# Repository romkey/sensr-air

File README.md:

# sensr-air

Hardware design and test firmware for a small air quality sensor PCB with:

| Sensor | Function | I2C address |
|--------|----------|-------------|
| Sensirion SGP41 | VOC index / NOx index | 0x59 |
| Sensirion STCC4 | CO2 | 0x64 (0x65 if ADDR is high) |
| Sensirion SFA40 | formaldehyde (HCHO) | 0x5D |
| Sensirion SHT40 | temperature / humidity | none — connected to the STCC4's private I2C bus and read through the STCC4 |
| Bosch BMV080 | PM1 / PM2.5 / PM10 | 0x54 |

Boards up to `hw/air-stcc4/0.3.0` carry an SGP40 (VOC only) instead of the
SGP41 and have no SFA40. The two SGP parts share address 0x59; the test
firmwares read the SGP4x feature set at startup to tell them apart, so one
build runs on either revision.

This is a 3.3 V board with no voltage regulator — don't use it with 5 V
circuits. To simplify it, the board is opinionated about I2C
addresses and doesn't expose address selection pins for chips that
have them. For reliability I don't recommend putting too many chips on
one I2C bus.

## AI Disclosure

The board was designed by a human. CI and firmware were generated by AI.

## Hardware

Board designs live under [hw/](hw/), one subdirectory per board with a
subdirectory per version:

- [hw/air-stcc4/](hw/air-stcc4/) — STCC4 + SHT40 breakout
- [hw/air/](hw/air/) — earlier SCD40 + BME680 board

### KiCAD CI

The [KiCAD workflow](.github/workflows/kicad.yml) runs
[ci/kicad-check.sh](ci/kicad-check.sh), which runs ERC on every schematic and
DRC on every PCB of the latest version of each board under `hw/`. Only errors
fail the check; warnings are ignored. Boards or versions containing a
`.ci-kicad-ignore` file are skipped.

Run it locally with KiCAD 8+ installed:

```sh
./ci/kicad-check.sh
```

### kilint CI

The [kilint workflow](.github/workflows/kilint.yml) runs
[kilint](https://github.com/romkey/kilint), a linter for KiCAD project
conventions that ERC and DRC don't cover (title blocks, reference designators,
mounting holes, part number fields, net classes, and so on). It runs only when
[BOFFF.md](BOFFF.md) is present, and lints the single board that BOFFF.md's
`repository_path` points at via [ci/kilint-check.sh](ci/kilint-check.sh).
Older boards under `hw/` predate these conventions and are not checked.

Rule configuration lives in [.kilint.yml](.kilint.yml). kilint has no tagged
releases yet, so the workflow installs it from `main`; pin `KILINT_REF` in the
workflow once it does.

Run it locally:

```sh
pip install git+https://github.com/romkey/kilint
./ci/kilint-check.sh
```

### BOFFF

[BOFFF.md](BOFFF.md) is this board's machine-readable fabrication/form-factor
description (Bill of Form, Fit and Features) - it's a tldr; for
important facts about the board. The [BOFFF workflow](.github/workflows/bofff.yml) does nothing but
assert the file exists, so the BOFFF badge above is green whenever the repo
carries one.

## Test firmware

Each firmware directory contains a test program that exercises all of the
board's sensors, a README, and (where possible) a docker compose file to
build it. All of them print/report readings from each sensor so you can
verify a freshly assembled board.

| Directory | Platform | SGP41 | STCC4 | SFA40 | SHT40 (via STCC4) | BMV080 |
|-----------|----------|-------|-------|-------|-------------------|--------|
| [firmware/circuitpython/](firmware/circuitpython/) | CircuitPython 9+ | yes | yes | yes³ | yes | presence check only¹ |
| [firmware/arduino/](firmware/arduino/) | Arduino / ESP32 | yes | yes | yes | yes | yes |
| [firmware/esphome/](firmware/esphome/) | ESPHome / ESP32 | yes | yes² | yes⁴ | yes² | yes |

¹ Bosch only ships the BMV080 driver as closed-source precompiled static
libraries for specific MCU toolchains, so no CircuitPython driver exists.

² ESPHome has no upstream STCC4 support; this repo includes a local
[external component](firmware/esphome/components/stcc4/) for it.

³ Via [romkey/circuitpython-sfa40](https://github.com/romkey/circuitpython-sfa40).

⁴ ESPHome's `sfa40` component landed upstream after 2026.8, so the ESPHome
build uses the beta channel until a stable release includes it.

CI builds all three firmwares on every push
([CircuitPython](.github/workflows/circuitpython.yml),
[Arduino](.github/workflows/arduino.yml),
[ESPHome](.github/workflows/esphome.yml)).

## License

Hardware designs are licensed under the
[CERN Open Hardware Licence v2 Permissive](https://ohwr.org/cern_ohl_p_v2.txt).
Firmware is licensed under the [MIT License](https://opensource.org/license/mit).

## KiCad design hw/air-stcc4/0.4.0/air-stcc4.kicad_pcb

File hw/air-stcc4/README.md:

# Sensr Air STCC4

This breakout board has Sensirion's new CO2 sensor, the STCC4, as well as an SHT40 temperature/humidity sensor. The board also has two STEMMAQT/Qwiic connectors and a five pin header with power, I2C and the STCC4's address select pin.

This is a 3.3V board and has no voltage regulator, so don't use it with 5V circuits!

It also has a power LED.

The STCC4 has a selectable I2C address depending on the state of the ADDR line.  The ADDR line has a weak pulldown resistor so that the STCC4's default I2C address is 0x64. If ADDR is high, the address will be 0x65.

The SHT40 is not directly accessible from the I2C bus. Instead it connects to a private second I2C bus with the STCC4. Its values may be read through the STCC4.

## 0.1.0 Hardware

## Firmware

Example program in CircuitPython:

```
import time
import board
import busio
from adafruit_stcc4 import STCC4

# Initialize I2C bus
i2c = busio.I2C(board.SCL, board.SDA)

# Initialize STCC4 sensor
sensor = STCC4(i2c)

print("STCC4 CO2 Sensor Test")
print("=" * 50)

# Print sensor information
print(f"Serial Number: {sensor.serial_number}")
print(f"Firmware Version: {sensor.firmware_version[0]}.{sensor.firmware_version[1]}")
print(f"SHT40 Available: {sensor.sht40_available}")
print()

# Read CO2, temperature, and humidity measurements
print("Environmental Measurements:")
print("-" * 30)

while True:
    co2 = sensor.co2
    print(f"Reading {i+1:2d}: CO2: {co2:6.1f} ppm")
        
    if sensor.sht40_available:
       temperature, humidity = sensor.measure_temperature_humidity()
       print(f"           Temp: {temperature:5.1f}°C, Humidity: {humidity:5.1f}%")
    else:
       print("           SHT40 not available - no temp/humidity data")
        
    print()
        
    time.sleep(2)  # Wait 2 seconds between readings

print("Test complete!")
```

## License

Please see the top level [README](../../README.md) for license information.

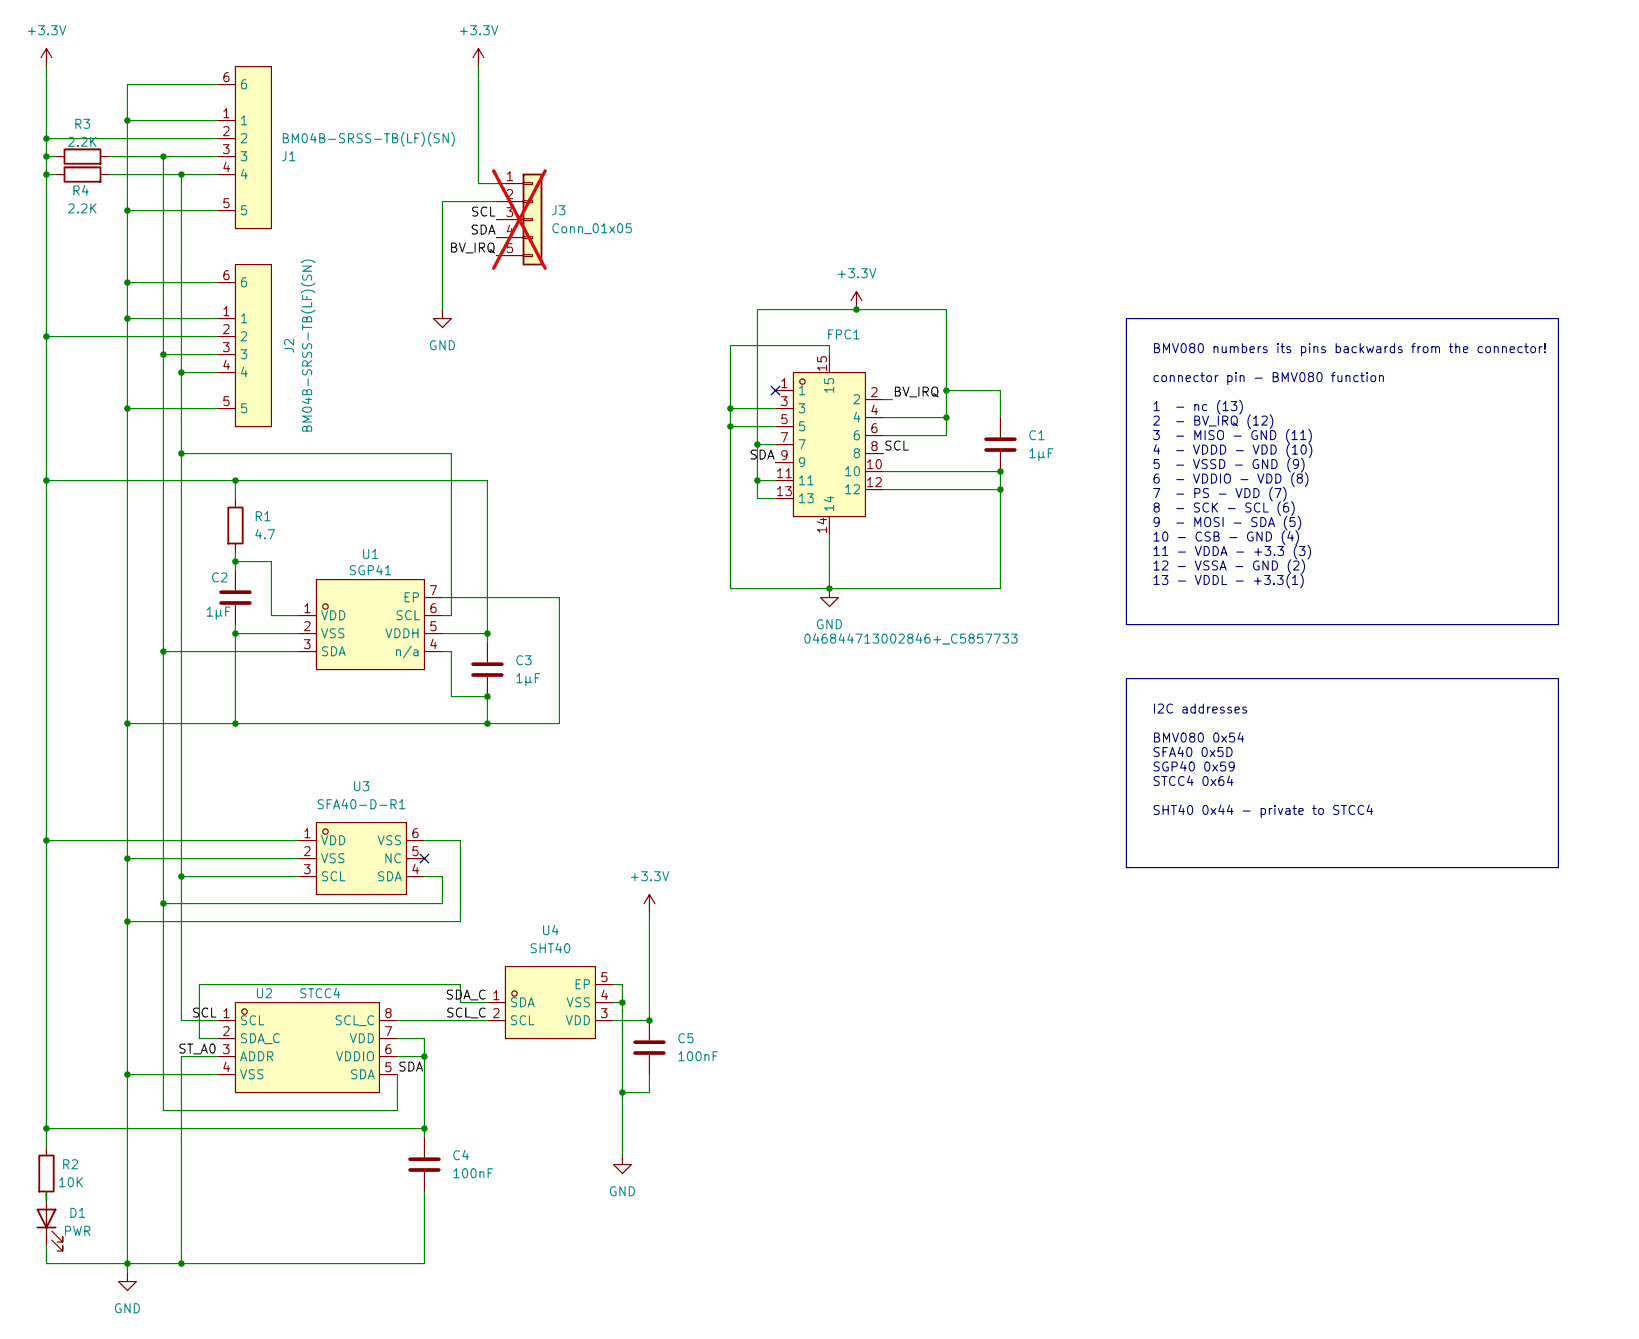
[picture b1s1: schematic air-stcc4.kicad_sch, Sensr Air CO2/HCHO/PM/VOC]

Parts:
C1, C2, C3: 1µF; C_0402_1005Metric_Pad0.74x0.62mm_HandSolder; LCSC Part C52923
C4, C5: 100nF; C_0402_1005Metric_Pad0.74x0.62mm_HandSolder; LCSC Part C1525
D1: PWR; LED_0603_1608Metric_Pad1.05x0.95mm_HandSolder; LCSC Part C2286
FPC1: 046844713002846+_C5857733; FPC-SMD_13P-P0.60_046844713002846-1; LCSC Part C5857733
J1, J2: BM04B-SRSS-TB(LF)(SN); CONN-SMD_4P-P1.00_SM04B-SRSS-TB-LF-SN; LCSC Part C160404
J3: Conn_01x05; PinSocket_1x05_P2.54mm_Vertical; not fitted
R1: 4.7; R_0603_1608Metric_Pad0.98x0.95mm_HandSolder; LCSC Part C23164
R2: 10K; R_0402_1005Metric_Pad0.72x0.64mm_HandSolder; LCSC Part C25744
R3, R4: 2.2K; R_0402_1005Metric_Pad0.72x0.64mm_HandSolder; LCSC Part C25879
U1: SGP41; DFN-6_L2.4-W2.4-P0.80-TL-EP; LCSC Part C3659325
U2: STCC4; LAG-8_L4.0-W3.0-P1.15-TL; LCSC Part C49191471
U3: SFA40-D-R1; SENSOR-SMD_SFA40-D-R1; LCSC Part C54863645
U4: SHT40; DFN-4_L1.5-W1.5-P0.80-TL-EP; LCSC Part C2848306

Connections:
+3.3V: C1.1, C3.1, C4.1, C5.1, FPC1.4, FPC1.6, FPC1.7, FPC1.11, FPC1.13, J1.2, J2.2, J3.1, R1.1, R2.1, R3.1, R4.1, U1.5 (VDDH), U2.6 (VDDIO), U2.7 (VDD), U3.1 (VDD), U4.3 (VDD)
/BV_IRQ: FPC1.2, J3.5
/SCL: FPC1.8, J1.4, J2.4, J3.3, R4.2, U1.6 (SCL), U2.1 (SCL), U3.3 (SCL)
/SCL_C: U2.8 (SCL_C), U4.2 (SCL)
/SDA: FPC1.9, J1.3, J2.3, J3.4, R3.2, U1.3 (SDA), U2.5 (SDA), U3.4 (SDA)
/SDA_C: U2.2 (SDA_C), U4.1 (SDA)
GND: C1.2, C2.2, C3.2, C4.2, C5.2, D1.1 (K), FPC1.3, FPC1.5, FPC1.10, FPC1.12, FPC1.14, FPC1.15, J1.1, J1.5, J1.6, J2.1, J2.5, J2.6, J3.2, U1.2 (VSS), U1.4 (n/a), U1.7 (EP), U2.3 (ADDR), U2.4 (VSS), U3.2 (VSS), U3.6 (VSS), U4.4 (VSS), U4.5 (EP)
unnamed: D1.2 (A), R2.2
unnamed: C2.1, R1.2, U1.1 (VDD)

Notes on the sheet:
BMV080 numbers its pins backwards from the connector! connector pin - BMV080 function 1 - nc (13) 2 - BV_IRQ (12) 3 - MISO - GND (11) 4 - VDDD - VDD (10) 5 - VSSD - GND (9) 6 - VDDIO - VDD (8) 7 - PS - VDD (7) 8 - SCK - SCL (6) 9 - MOSI - SDA (5) 10 - CSB - GND (4) 11 - VDDA - +3.3 (3) 12 - VSSA - 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
I2C addresses BMV080 0x54 SFA40 0x5D SGP40 0x59 STCC4 0x64 SHT40 0x44 - private to STCC4

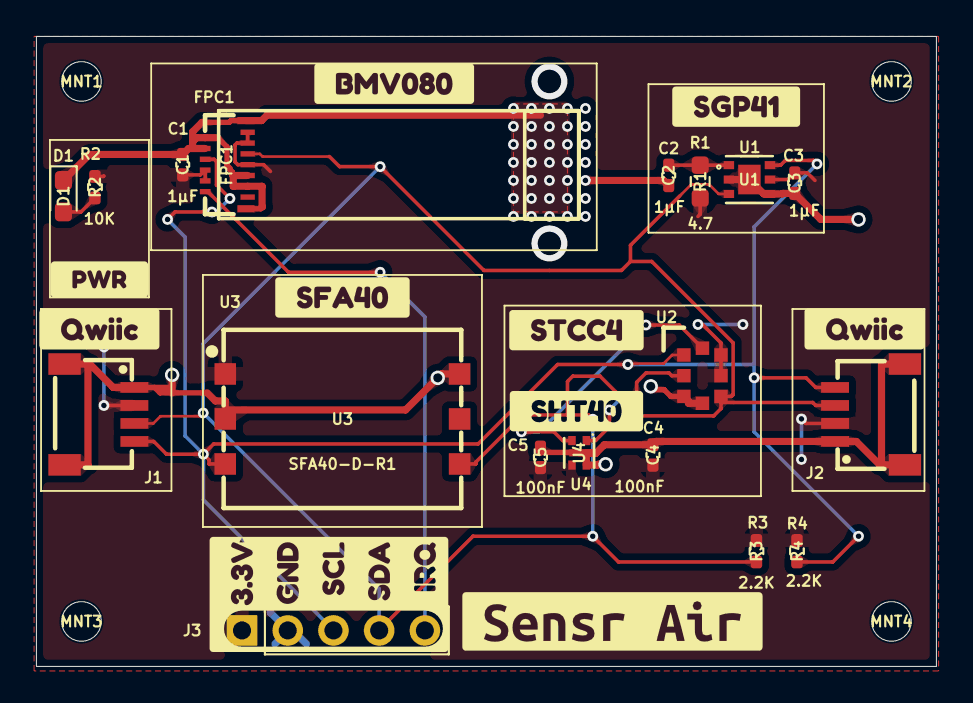
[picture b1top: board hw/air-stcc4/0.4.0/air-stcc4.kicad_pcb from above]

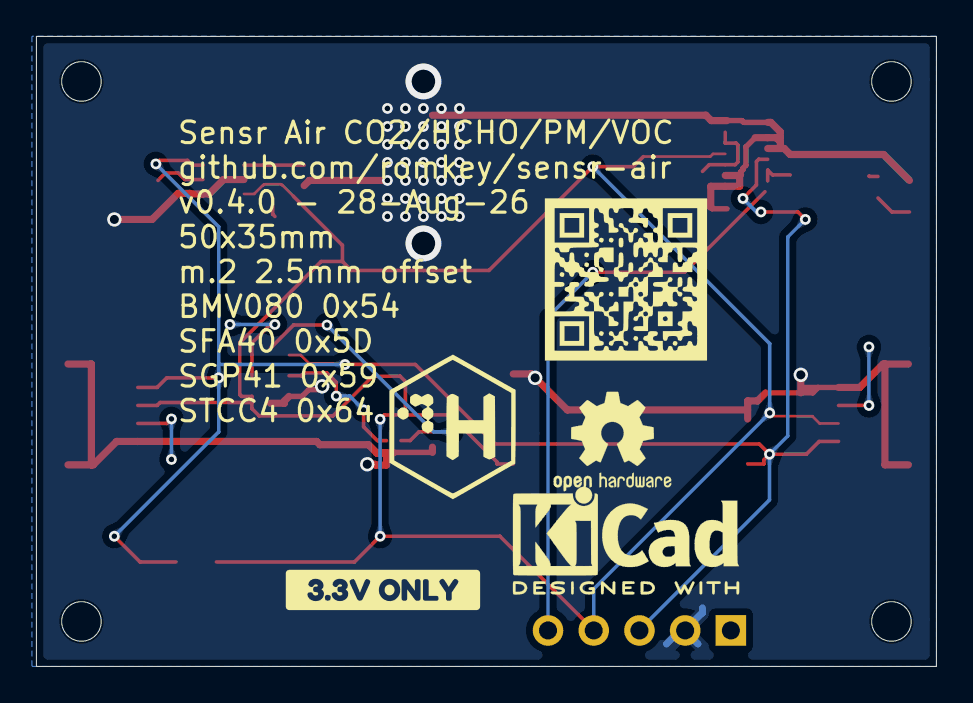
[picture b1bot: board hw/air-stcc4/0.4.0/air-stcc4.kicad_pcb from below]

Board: 2 copper layers, 50.0 x 35.0 mm, 37 parts (5 on the bottom side), 9 nets.

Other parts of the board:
GRPH1: LOGO
GRPH2: CTRLH Logo
GRPH3: OSHW-Logo2_7.3x6mm_SilkScreen
GRPH4: KiCad-Logo2_5mm_SilkScreen
MNT1, MNT2, MNT3, MNT4: MountingHole_2.2mm_M2
kobee-studio-1: GRPH4; kobee-studio-6A887D6C
kobee-studio-2: GRPH5; kobee-studio-6A887DEC
kobee-studio-3: G***; kobee-studio-6A91A728
kobee-studio-4: GRPH8; kobee-studio-6A887E41
kobee-studio-5: GRPH7; kobee-studio-6A887E5F
kobee-studio-6: GRPH9; kobee-studio-6A887E13
kobee-studio-6A91B03A: G***; kobee-studio-6A91B03A
kobee-studio-7: GRPH6; kobee-studio-6A8882DF
kobee-studio-8: GRPH10; kobee-studio-6A887E32
kobee-studio-9: G***; kobee-studio-6A91A7CE
kobee-studio-10: GRPH11; kobee-studio-6A887EAF

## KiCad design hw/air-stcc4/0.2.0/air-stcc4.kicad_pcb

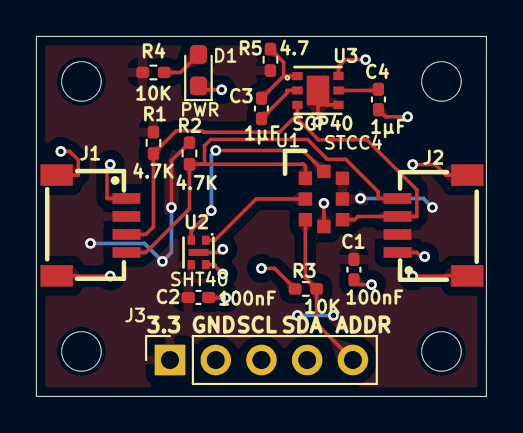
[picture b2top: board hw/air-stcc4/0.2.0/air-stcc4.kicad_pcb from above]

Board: 2 copper layers, 25.0 x 20.0 mm, 21 parts (1 on the bottom side), 11 nets.

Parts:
C1, C2: 100nF; C_0402_1005Metric_Pad0.74x0.62mm_HandSolder
C3, C4: 1µF; C_0402_1005Metric_Pad0.74x0.62mm_HandSolder
D1: PWR; LED_0603_1608Metric_Pad1.05x0.95mm_HandSolder
GRPH1: CTRLH Logo
J1, J2: BM04B-SRSS-TB(LF)(SN); CONN-SMD_4P-P1.00_SM04B-SRSS-TB-LF-SN
J3: Conn_01x05; PinSocket_1x05_P2.54mm_Vertical
M1, M2, M3, M4: MountingHole_2.2mm_M2
R1, R2: 4.7K; R_0402_1005Metric_Pad0.72x0.64mm_HandSolder
R3, R4: 10K; R_0402_1005Metric_Pad0.72x0.64mm_HandSolder
R5: 4.7; R_0402_1005Metric_Pad0.72x0.64mm_HandSolder
U1: STCC4; LAG-8_L4.0-W3.0-P1.15-TL
U2: SHT40; DFN-4_L1.5-W1.5-P0.80-TL-EP
U3: SGP40; DFN-6_L2.4-W2.4-P0.80-TL-EP

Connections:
+3.3V: C1.1, C2.1, J1.2, J2.2, J3.1, R1.1, R2.1, R4.1, R5.1, U1.6 (VDDIO), U1.7 (VDD), U2.3 (VDD)
/ADDR: J3.5, R3.1, U1.3 (ADDR)
/SCL_C: U1.8 (SCL_C), U2.2 (SCL)
/SDA_C: U1.2 (SDA_C), U2.1 (SDA)
GND: C1.2, C2.2, C4.2, D1.1 (K), J1.1, J1.5, J1.6, J2.1, J2.5, J2.6, J3.2, R3.2, U1.4 (VSS), U2.4 (VSS), U2.5 (EP), U3.4 (n/a), U3.6 (SCL), U3.7 (GND)
unnamed: D1.2 (A), R4.2
unnamed: J1.4, J2.4, R2.2, U1.1 (SCL)
unnamed: J1.3, J2.3, R1.2, U1.5 (SDA), U3.3 (SDA)
unnamed: C3.1, R5.2, U3.1 (VDD)
unnamed: C4.1, U3.5 (VDDH)
unnamed: C3.2, U3.2 (VSS)

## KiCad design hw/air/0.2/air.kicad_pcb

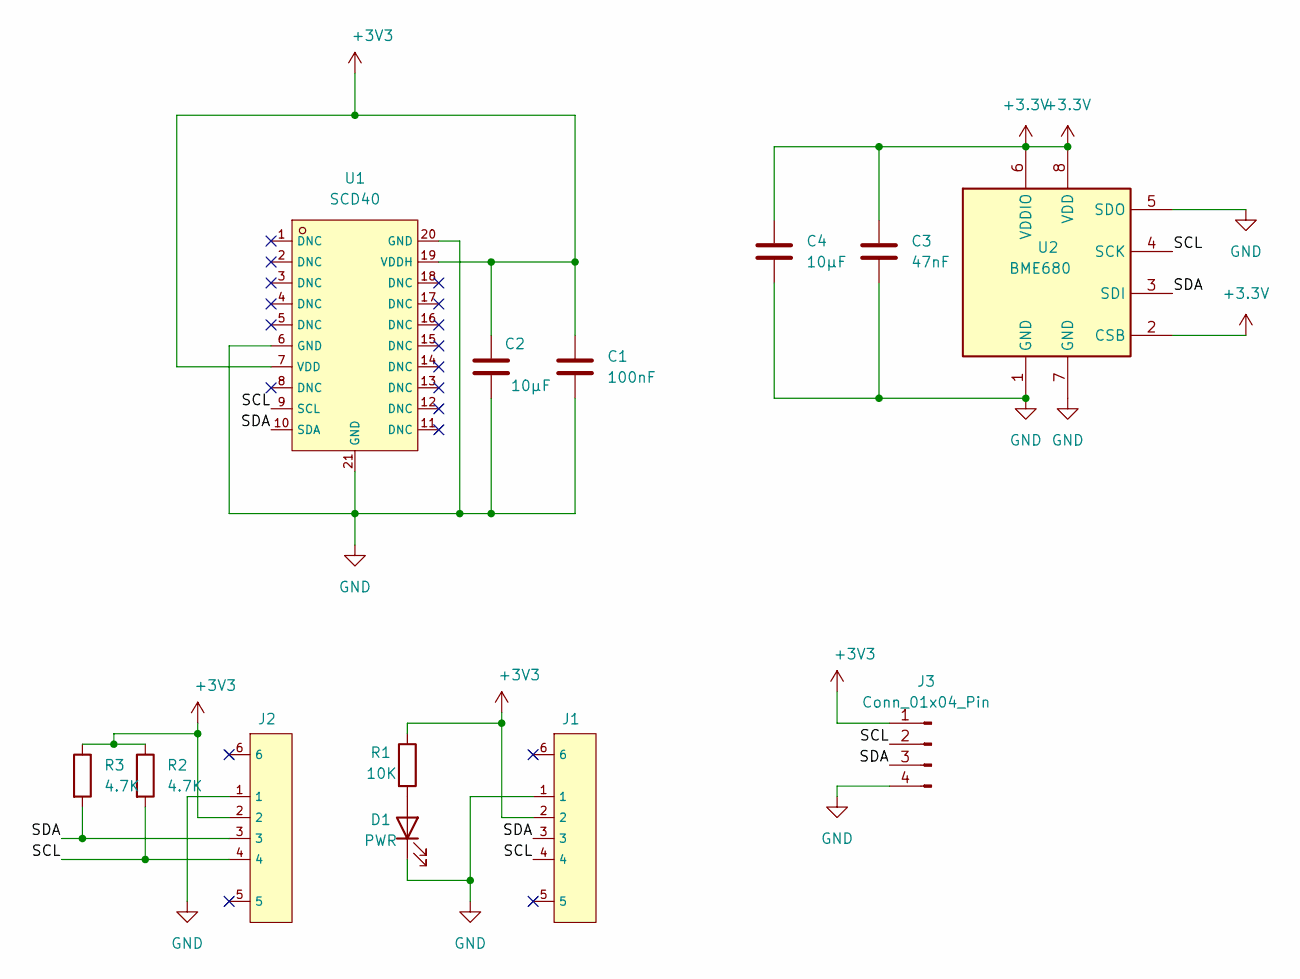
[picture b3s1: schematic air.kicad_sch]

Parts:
C1: 100nF; C_0805_2012Metric_Pad1.18x1.45mm_HandSolder; MPN C1711
C2, C4: 10µF; C_0805_2012Metric_Pad1.18x1.45mm_HandSolder; MPN C342724
C3: 47nF; C_0805_2012Metric_Pad1.18x1.45mm_HandSolder; MPN C1745
D1: PWR; LED_0805_2012Metric; LCSC C84256
J1, J2: SM04B-SRSS-TB_(LF)(SN); CONN-SMD_4P-P1.00_SM04B-SRSS-TB-LF-SN; LCSC C160404
J3: Conn_01x04_Pin; PinHeader_1x04_P2.54mm_Vertical
R1: 10K; R_0805_2012Metric_Pad1.20x1.40mm_HandSolder; LCSC C17414
R2, R3: 4.7K; R_0805_2012Metric_Pad1.20x1.40mm_HandSolder; MPN C105427
U1: SCD40; LGA-20_L10.1-W10.1-P1.25-TL; LCSC C3659421
U2: BME680; Bosch_LGA-8_3x3mm_P0.8mm_ClockwisePinNumbering; MPN C125972

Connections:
+3.3V: C3.1, C4.1, U2.2 (CSB), U2.6 (VDDIO), U2.8 (VDD)
+3V3: C1.1, C2.1, J1.2, J2.2, J3.1, R1.1, R2.1, R3.1, U1.7 (VDD), U1.19 (VDDH)
/SCL: J1.4, J2.4, J3.2, R2.2, U1.9 (SCL), U2.4 (SCK)
/SDA: J1.3, J2.3, J3.3, R3.2, U1.10 (SDA), U2.3 (SDI)
GND: C1.2, C2.2, C3.2, C4.2, D1.1 (K), J1.1, J2.1, J3.4, U1.6 (GND), U1.20 (GND), U1.21 (GND), U2.1 (GND), U2.5 (SDO), U2.7 (GND)
unnamed: D1.2 (A), R1.2

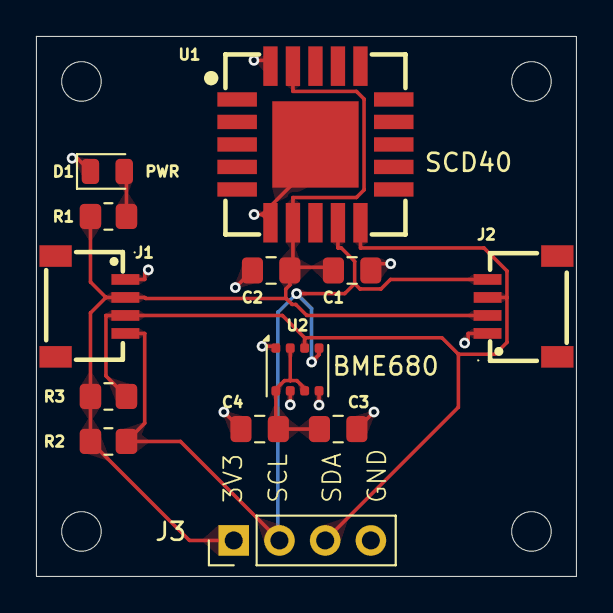
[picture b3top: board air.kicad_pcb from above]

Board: 2 copper layers, 30.0 x 30.0 mm, 17 parts (0 on the bottom side), 6 nets.

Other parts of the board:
M1, M2, M3, M4: MountingHole_2.2mm_M2

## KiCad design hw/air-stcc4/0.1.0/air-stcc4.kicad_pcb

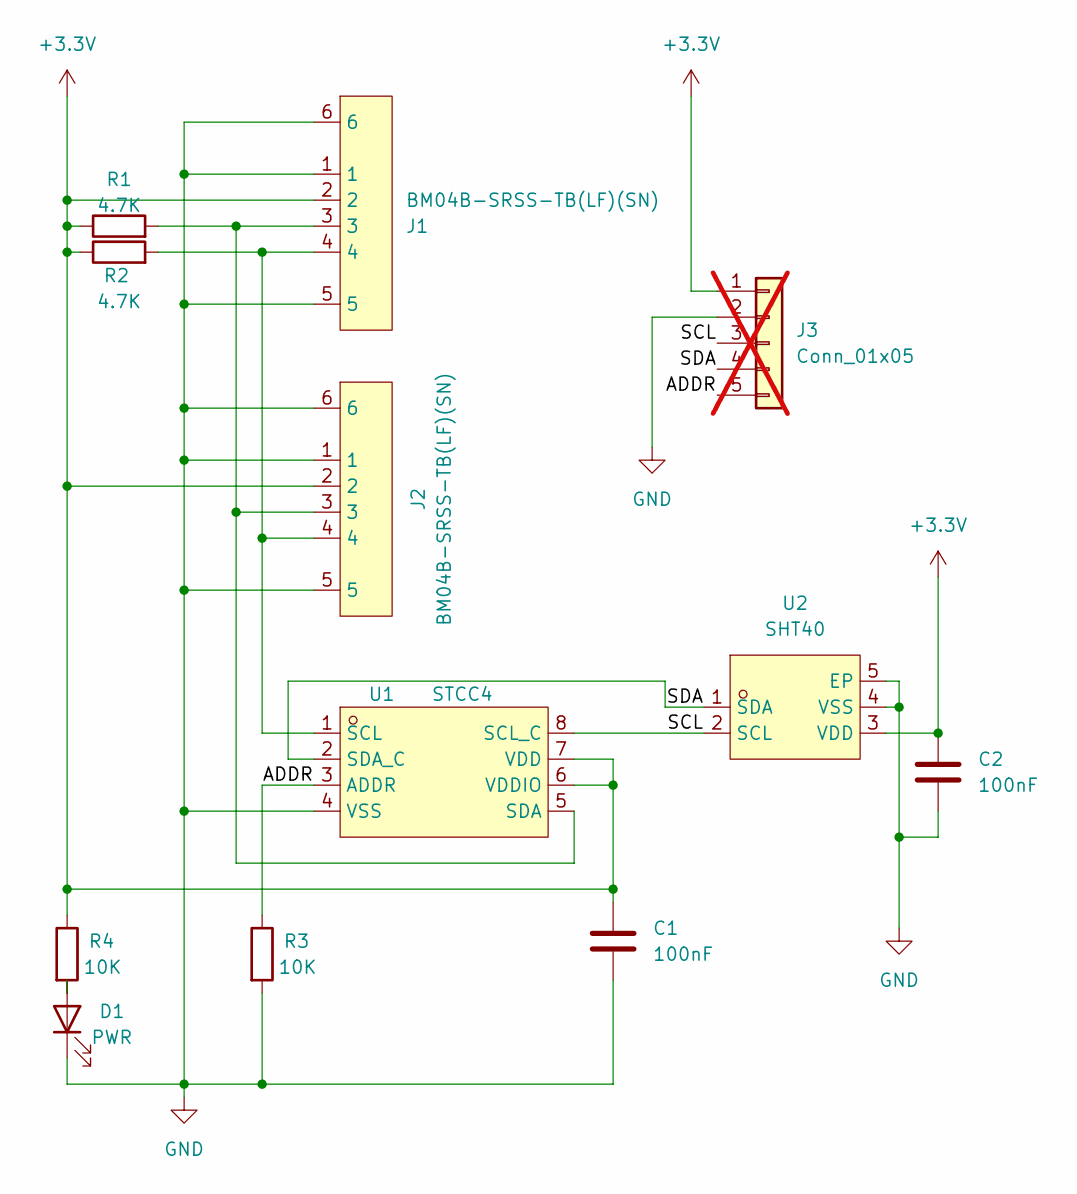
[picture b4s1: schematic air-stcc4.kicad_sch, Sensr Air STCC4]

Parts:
C1, C2: 100nF; C_0603_1608Metric_Pad1.08x0.95mm_HandSolder; MPN C14663
D1: PWR; LED_0603_1608Metric_Pad1.05x0.95mm_HandSolder; LCSC C2286
J1, J2: BM04B-SRSS-TB(LF)(SN); CONN-SMD_4P-P1.00_SM04B-SRSS-TB-LF-SN; LCSC Part C160404
J3: Conn_01x05; PinSocket_1x05_P2.54mm_Vertical; not fitted
R1, R2: 4.7K; R_0603_1608Metric_Pad0.98x0.95mm_HandSolder; MPN C23162
R3, R4: 10K; R_0603_1608Metric_Pad0.98x0.95mm_HandSolder; LCSC C25804
U1: STCC4; LAG-8_L4.0-W3.0-P1.15-TL; LCSC Part C49191471
U2: SHT40; DFN-4_L1.5-W1.5-P0.80-TL-EP; LCSC Part C7461861

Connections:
+3.3V: C1.1, C2.1, J1.2, J2.2, J3.1, R1.1, R2.1, R4.1, U1.6 (VDDIO), U1.7 (VDD), U2.3 (VDD)
/ADDR: J3.5, R3.1, U1.3 (ADDR)
/SCL: J3.3, U1.8 (SCL_C), U2.2 (SCL)
/SDA: J3.4, U1.2 (SDA_C), U2.1 (SDA)
GND: C1.2, C2.2, D1.1 (K), J1.1, J1.5, J1.6, J2.1, J2.5, J2.6, J3.2, R3.2, U1.4 (VSS), U2.4 (VSS), U2.5 (EP)
unnamed: D1.2 (A), R4.2
unnamed: J1.4, J2.4, R2.2, U1.1 (SCL)
unnamed: J1.3, J2.3, R1.2, U1.5 (SDA)

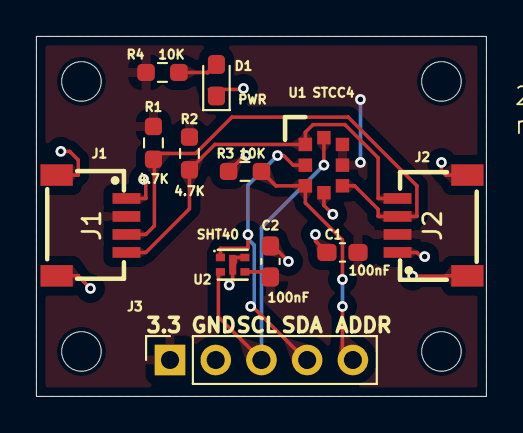
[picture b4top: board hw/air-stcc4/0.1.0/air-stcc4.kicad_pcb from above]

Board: 2 copper layers, 25.0 x 20.0 mm, 16 parts (0 on the bottom side), 8 nets.

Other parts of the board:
M1, M2, M3, M4: MountingHole_2.2mm_M2

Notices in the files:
hw/air-stcc4/0.1.0/air-stcc4.kicad_pcb:
License: CERN-OHL-S https://ohwr.org/cern_ohl_s_v2.pdf
hw/air-stcc4/0.1.0/air-stcc4.kicad_sch:
License: CERN-OHL-S License: CERN-OHL-S https://ohwr.org/cern_ohl_s_v2.pdf
